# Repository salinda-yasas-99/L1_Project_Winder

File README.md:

# The Winder
Level 01 hardware project_ University of Moratuwa

Here is the system that is able to automate the process of winding transformers. Also, the system is able to measure transformer bobbin parameters and decide on relevant wire gauges according to the transformer input and output.

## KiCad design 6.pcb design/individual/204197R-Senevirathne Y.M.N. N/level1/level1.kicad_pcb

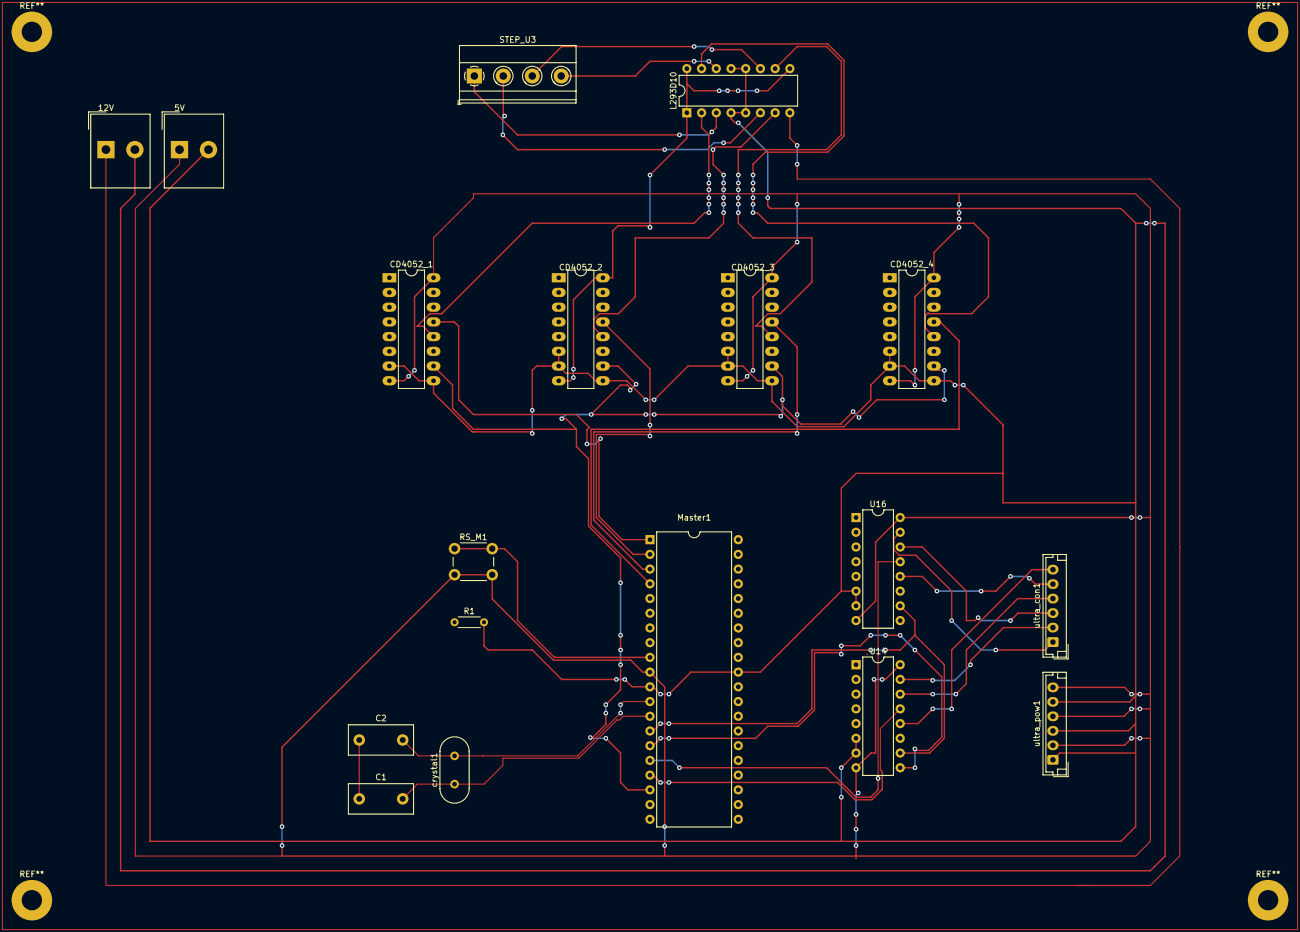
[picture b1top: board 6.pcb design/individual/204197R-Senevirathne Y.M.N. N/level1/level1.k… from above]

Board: 2 copper layers, 18 parts (0 on the bottom side), 30 nets.

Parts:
5V: 5V; Altech_AK300_1x02_P5.00mm_45-Degree
12V: 12V; Altech_AK300_1x02_P5.00mm_45-Degree
C1, C2: 22 uf; C_Disc_D11.0mm_W5.0mm_P7.50mm
CD4052_1, CD4052_2, CD4052_3, CD4052_4: CD4052B; DIP-16_W7.62mm_LongPads
L293D10: L293D; DIP-16_W7.62mm
Master1: ATmega32-16P; DIP-40_W15.24mm
R1: 1k; R_Axial_DIN0204_L3.6mm_D1.6mm_P5.08mm_Horizontal
RS_M1: SW_Push; SW_PUSH_6mm_H7.3mm
STEP_U3: Screw_Terminal_01x04; TerminalBlock_Phoenix_MKDS-1,5-4_1x04_P5.00mm_Horizontal
U14, U16: CD4052B; DIP-16_W7.62mm
crystal1: 16Mhz; Crystal_HC49-4H_Vertical
ultra_con1: Conn_01x06_Female; JST_EH_B6B-EH-A_1x06_P2.50mm_Vertical
ultra_pow1: Conn_01x06_Female; JST_EH_B6B-EH-A_1x06_P2.50mm_Vertical

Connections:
5VCC: 5V.1, CD4052_1.8 (VSS), CD4052_1.16 (VDD), CD4052_2.8 (VSS), CD4052_2.16 (VDD), CD4052_3.8 (VSS), CD4052_3.16 (VDD), CD4052_4.8 (VSS), CD4052_4.16 (VDD), L293D10.1 (EN1,2), L293D10.9 (EN3,4), L293D10.16 (VCC1), Master1.10 (VCC), RS_M1.2, U14.8 (VSS), U14.16 (VDD), U16.8 (VSS), U16.16 (VDD), ultra_pow1.2, ultra_pow1.4, ultra_pow1.6
12VCC: 12V.1, L293D10.8 (VCC2)
GND: 5V.2, 12V.2, CD4052_1.6 (INH), CD4052_1.7 (VEE), CD4052_1.9 (B), CD4052_2.6 (INH), CD4052_2.7 (VEE), CD4052_2.9 (B), CD4052_3.6 (INH), CD4052_3.7 (VEE), CD4052_3.9 (B), CD4052_4.6 (INH), CD4052_4.7 (VEE), CD4052_4.9 (B), L293D10.4 (GND), L293D10.5 (GND), L293D10.12 (GND), L293D10.13 (GND), Master1.11 (GND), Master1.31 (GND), R1.2, U14.6 (INH), U14.7 (VEE), U16.6 (INH), U16.7 (VEE), ultra_pow1.1, ultra_pow1.3, ultra_pow1.5
unnamed: C1.1, C2.1
Reset_M: Master1.9 (~RESET), R1.1, RS_M1.1
STEP2_demux_IN1: CD4052_1.13 (X), Master1.1 (PB0)
STEP2_demux_IN2: CD4052_2.13 (X), Master1.2 (PB1)
STEP2_demux_IN3: CD4052_3.13 (X), Master1.3 (PB2)
STEP2_demux_IN4: CD4052_4.13 (X), Master1.4 (PB3)
Stepper_demux_selector: CD4052_1.10 (A), CD4052_2.10 (A), CD4052_3.10 (A), CD4052_4.10 (A), Master1.18 (PD4)
U1_Echo: U16.12 (X0), ultra_con1.5
U1_Tri: U14.12 (X0), ultra_con1.6
U2_Echo: U16.14 (X1), ultra_con1.3
U2_Tri: U14.14 (X1), ultra_con1.4
U3_Echo: U16.15 (X2), ultra_con1.1
U3_Tri: U14.15 (X2), ultra_con1.2
U3_in_1: CD4052_1.12 (X0), L293D10.2 (1A)
U3_in_2: CD4052_2.12 (X0), L293D10.7 (2A)
U3_in_3: CD4052_3.12 (X0), L293D10.10 (3A)
U3_in_4: CD4052_4.12 (X0), L293D10.15 (4A)
U3_out1: L293D10.3 (1Y), STEP_U3.1
U3_out2: L293D10.6 (2Y), STEP_U3.2
U3_out3: L293D10.11 (3Y), STEP_U3.3
U3_out4: L293D10.14 (4Y), STEP_U3.4
Ultra_demux_input: Master1.17 (PD3), U14.13 (X)
Ultra_mux_input: Master1.16 (PD2), U16.13 (X)
ultra_S1: Master1.14 (PD0), U14.10 (A), U16.10 (A)
ultra_S2: Master1.15 (PD1), U14.9 (B), U16.9 (B)
xtal1_M: C1.2, Master1.13 (XTAL1), crystal1.1
xtal2_M: C2.2, Master1.12 (XTAL2), crystal1.2

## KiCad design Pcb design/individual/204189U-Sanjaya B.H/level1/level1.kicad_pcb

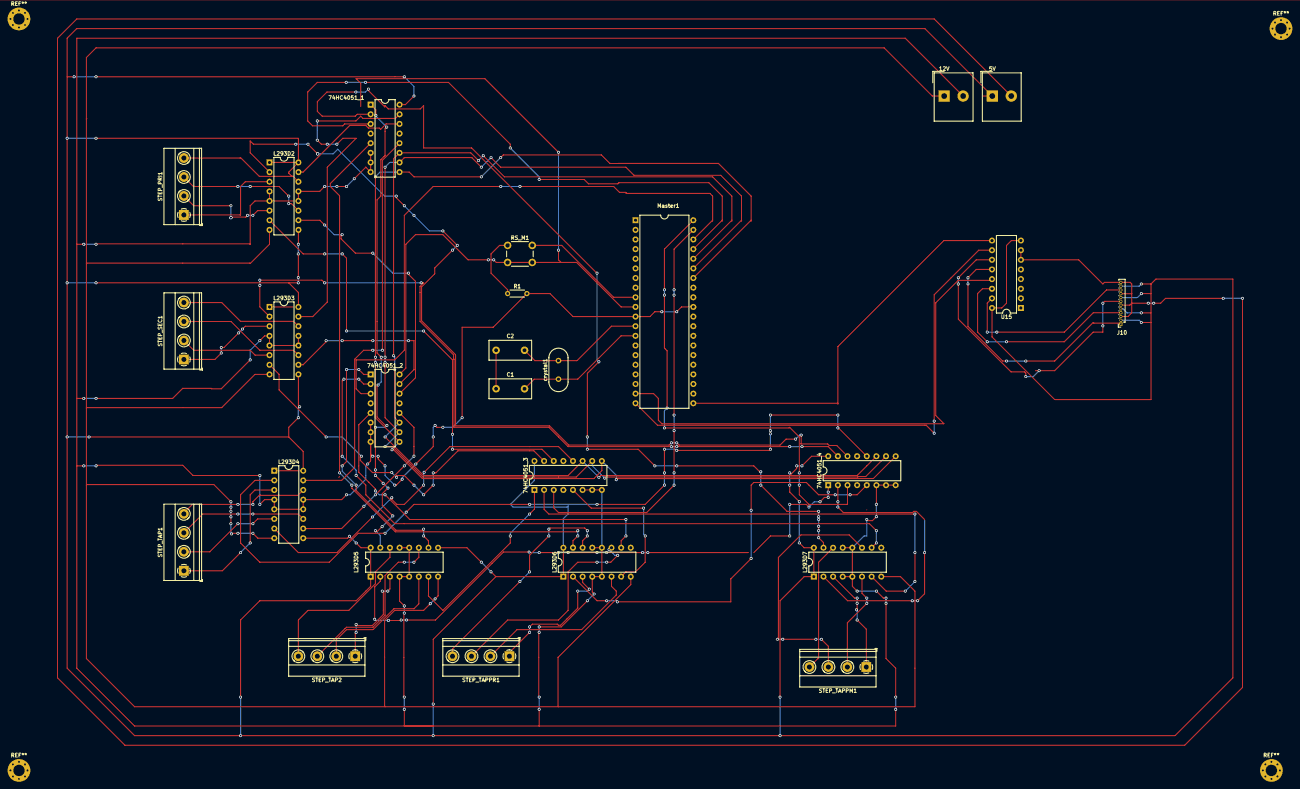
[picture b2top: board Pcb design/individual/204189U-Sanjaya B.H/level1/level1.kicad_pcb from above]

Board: 2 copper layers, 26 parts (0 on the bottom side), 41 nets.

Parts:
5V: 5V; Altech_AK300_1x02_P5.00mm_45-Degree
12V: 12V; Altech_AK300_1x02_P5.00mm_45-Degree
74HC4051_1, 74HC4051_2, 74HC4051_3, 74HC4051_4: 74HCT4051; DIP-16_W7.62mm
C1, C2: 22 uf; C_Disc_D11.0mm_W5.0mm_P7.50mm
J10: Servo; PinSocket_1x12_P1.00mm_Vertical
L293D2, L293D3, L293D4, L293D5, L293D6, L293D7: L293D; DIP-16_W7.62mm
Master1: ATmega32-16P; DIP-40_W15.24mm
R1: 1k; R_Axial_DIN0204_L3.6mm_D1.6mm_P5.08mm_Horizontal
RS_M1: SW_Push; SW_PUSH_6mm_H7.3mm
STEP_PRI1: Screw_Terminal_01x04; TerminalBlock_Phoenix_MKDS-1,5-4_1x04_P5.00mm_Horizontal
STEP_SEC1: Screw_Terminal_01x04; TerminalBlock_Phoenix_MKDS-1,5-4_1x04_P5.00mm_Horizontal
STEP_TAP1, STEP_TAP2: Screw_Terminal_01x04; TerminalBlock_Phoenix_MKDS-1,5-4_1x04_P5.00mm_Horizontal
STEP_TAPPM1: Screw_Terminal_01x04; TerminalBlock_Phoenix_MKDS-1,5-4_1x04_P5.00mm_Horizontal
STEP_TAPPR1: Screw_Terminal_01x04; TerminalBlock_Phoenix_MKDS-1,5-4_1x04_P5.00mm_Horizontal
U15: CD4052B; DIP-16_W7.62mm
crystal1: 16Mhz; Crystal_HC49-4H_Vertical

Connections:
5VCC: 5V.1, 74HC4051_1.16 (VCC), 74HC4051_2.16 (VCC), 74HC4051_3.16 (VCC), 74HC4051_4.16 (VCC), J10.2, J10.5, J10.8, J10.11, L293D2.1 (EN1,2), L293D2.9 (EN3,4), L293D2.16 (VCC1), L293D3.1 (EN1,2), L293D3.9 (EN3,4), L293D3.16 (VCC1), L293D4.1 (EN1,2), L293D4.9 (EN3,4), L293D4.16 (VCC1), L293D5.1 (EN1,2), L293D5.9 (EN3,4), L293D5.16 (VCC1), L293D6.1 (EN1,2), L293D6.9 (EN3,4), L293D6.16 (VCC1), L293D7.1 (EN1,2), L293D7.9 (EN3,4), L293D7.16 (VCC1), Master1.10 (VCC), RS_M1.2, U15.8 (VSS), U15.16 (VDD)
12VCC: 12V.1, L293D2.8 (VCC2), L293D3.8 (VCC2), L293D4.8 (VCC2), L293D5.8 (VCC2), L293D6.8 (VCC2), L293D7.8 (VCC2)
DEMUX_Servo_IN: Master1.19 (PD5), U15.13 (X)
DEMUX_Servo_S1: Master1.20 (PD6), U15.10 (A)
DEMUX_Servo_S2: Master1.21 (PD7), U15.9 (B)
DEMUX_Stepper_S1: 74HC4051_1.11 (S0), 74HC4051_2.11 (S0), 74HC4051_3.11 (S0), 74HC4051_4.11 (S0), Master1.36 (PA4)
DEMUX_Stepper_S2: 74HC4051_1.10 (S1), 74HC4051_2.10 (S1), 74HC4051_3.10 (S1), 74HC4051_4.10 (S1), Master1.35 (PA5)
DEMUX_Stepper_S3: 74HC4051_1.9 (S2), 74HC4051_2.9 (S2), 74HC4051_3.9 (S2), 74HC4051_4.9 (S2), Master1.34 (PA6)
GND: 5V.2, 12V.2, 74HC4051_1.6 (~E), 74HC4051_1.7 (VEE), 74HC4051_1.8 (GND), 74HC4051_2.6 (~E), 74HC4051_2.7 (VEE), 74HC4051_2.8 (GND), 74HC4051_3.6 (~E), 74HC4051_3.7 (VEE), 74HC4051_3.8 (GND), 74HC4051_4.6 (~E), 74HC4051_4.7 (VEE), 74HC4051_4.8 (GND), J10.3, J10.6, J10.9, J10.12, L293D2.4 (GND), L293D2.5 (GND), L293D2.12 (GND), L293D2.13 (GND), L293D3.4 (GND), L293D3.5 (GND), L293D3.12 (GND), L293D3.13 (GND), L293D4.4 (GND), L293D4.5 (GND), L293D4.12 (GND), L293D4.13 (GND), L293D5.4 (GND), L293D5.5 (GND), L293D5.12 (GND), L293D5.13 (GND), L293D6.4 (GND), L293D6.5 (GND), L293D6.12 (GND), L293D6.13 (GND), L293D7.4 (GND), L293D7.5 (GND), L293D7.12 (GND), L293D7.13 (GND), Master1.11 (GND), Master1.31 (GND), R1.2, U15.6 (INH), U15.7 (VEE)
unnamed: C1.1, C2.1
Pri_IN1: 74HC4051_4.14 (A1), L293D2.2 (1A)
Pri_IN2: 74HC4051_3.14 (A1), L293D2.7 (2A)
Pri_IN3: 74HC4051_2.14 (A1), L293D2.10 (3A)
Pri_IN4: 74HC4051_1.14 (A1), L293D2.15 (4A)
Reset_M: Master1.9 (~RESET), R1.1, RS_M1.1
Sec_IN1: 74HC4051_4.15 (A2), L293D3.2 (1A)
Sec_IN2: 74HC4051_3.15 (A2), L293D3.7 (2A)
Sec_IN3: 74HC4051_2.15 (A2), L293D3.10 (3A)
Sec_IN4: 74HC4051_1.15 (A2), L293D3.15 (4A)
Step_IN1: 74HC4051_4.3 (A), Master1.40 (PA0)
Step_IN2: 74HC4051_3.3 (A), Master1.39 (PA1)
Step_IN3: 74HC4051_2.3 (A), Master1.38 (PA2)
Step_IN4: 74HC4051_1.3 (A), Master1.37 (PA3)
TAPM_IN1: 74HC4051_4.2 (A6), L293D7.2 (1A)
TAPM_IN2: 74HC4051_3.2 (A6), L293D7.7 (2A)
TAPM_IN3: 74HC4051_2.2 (A6), L293D7.10 (3A)
TAPM_IN4: 74HC4051_1.2 (A6), L293D7.15 (4A)
TAPR_IN1: 74HC4051_4.5 (A5), L293D6.2 (1A)
TAPR_IN2: 74HC4051_3.5 (A5), L293D6.7 (2A)
TAPR_IN3: 74HC4051_2.5 (A5), L293D6.10 (3A)
TAPR_IN4: 74HC4051_1.5 (A5), L293D6.15 (4A)
Tape1_IN1: 74HC4051_4.12 (A3), L293D4.2 (1A)
Tape1_IN2: 74HC4051_3.12 (A3), L293D4.7 (2A)
Tape1_IN3: 74HC4051_2.12 (A3), L293D4.10 (3A)
Tape1_IN4: 74HC4051_1.12 (A3), L293D4.15 (4A)
Tape2_IN1: 74HC4051_4.1 (A4), L293D5.2 (1A)
Tape2_IN2: 74HC4051_3.1 (A4), L293D5.7 (2A)
Tape2_IN3: 74HC4051_2.1 (A4), L293D5.10 (3A)
Tape2_IN4: 74HC4051_1.1 (A4), L293D5.15 (4A)
xtal1_M: C1.2, Master1.13 (XTAL1), crystal1.1
xtal2_M: C2.2, Master1.12 (XTAL2), crystal1.2

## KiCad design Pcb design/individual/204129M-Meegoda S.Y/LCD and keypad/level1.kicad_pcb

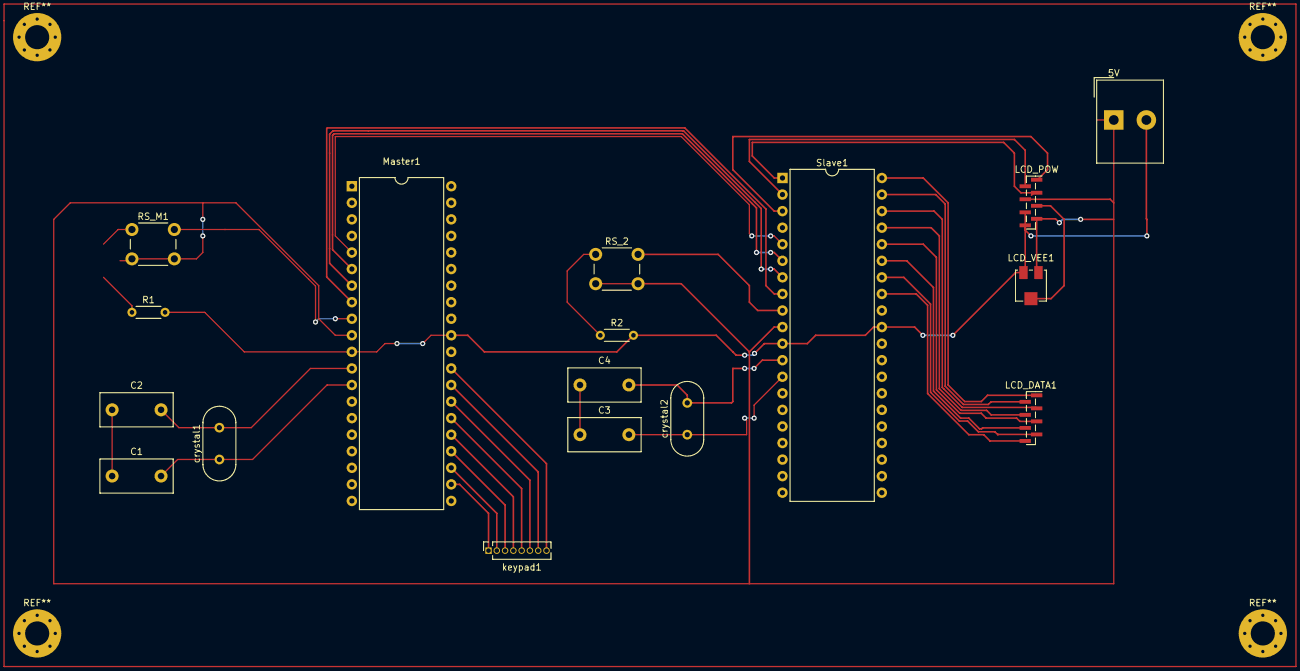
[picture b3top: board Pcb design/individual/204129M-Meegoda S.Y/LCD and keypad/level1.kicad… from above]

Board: 2 copper layers, 17 parts (0 on the bottom side), 34 nets.

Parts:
5V: 5V; Altech_AK300_1x02_P5.00mm_45-Degree
C1, C2, C3, C4: 22 uf; C_Disc_D11.0mm_W5.0mm_P7.50mm
LCD_DATA1: Conn_01x08_Female; PinHeader_1x08_P1.00mm_Vertical_SMD_Pin1Right
LCD_POW: Conn_01x08_Female; PinHeader_1x08_P1.00mm_Vertical_SMD_Pin1Right
LCD_VEE1: R_Potentiometer; Potentiometer_Bourns_3314J_Vertical
Master1: ATmega32-16P; DIP-40_W15.24mm
R1, R2: 1k; R_Axial_DIN0204_L3.6mm_D1.6mm_P5.08mm_Horizontal
RS_2: SW_Push; SW_PUSH_6mm_H7.3mm
RS_M1: SW_Push; SW_PUSH_6mm_H7.3mm
Slave1: ATmega32-16P; DIP-40_W15.24mm
crystal1, crystal2: 16Mhz; Crystal_HC49-4H_Vertical
keypad1: Conn_01x08_Female; PinSocket_1x08_P1.27mm_Vertical

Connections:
5VCC: 5V.1, LCD_POW.4, LCD_POW.7, LCD_VEE1.1, Master1.10 (VCC), RS_2.2, RS_M1.2, Slave1.10 (VCC)
En: LCD_POW.1, Slave1.3 (PB2)
GND: 5V.2, LCD_POW.6, LCD_POW.8, LCD_VEE1.3, Master1.11 (GND), Master1.31 (GND), R1.2, R2.2, Slave1.11 (GND), Slave1.31 (GND)
LCD_D0: LCD_DATA1.1, Slave1.40 (PA0)
LCD_D1: LCD_DATA1.2, Slave1.39 (PA1)
LCD_D2: LCD_DATA1.3, Slave1.38 (PA2)
LCD_D3: LCD_DATA1.4, Slave1.37 (PA3)
LCD_D4: LCD_DATA1.5, Slave1.36 (PA4)
LCD_D5: LCD_DATA1.6, Slave1.35 (PA5)
LCD_D6: LCD_DATA1.7, Slave1.34 (PA6)
LCD_D7: LCD_DATA1.8, Slave1.33 (PA7)
MISO: Master1.7 (PB6), Slave1.7 (PB6)
MOSI: Master1.6 (PB5), Slave1.6 (PB5)
unnamed: C1.1, C2.1
unnamed: C3.1, C4.1
RS: LCD_POW.3, Slave1.1 (PB0)
RW: LCD_POW.2, Slave1.2 (PB1)
Reset_M: Master1.9 (~RESET), R1.1, RS_M1.1
Reset_S: R2.1, RS_2.1, Slave1.9 (~RESET)
SCK: Master1.8 (PB7), Slave1.8 (PB7)
SS: Master1.5 (PB4), Slave1.5 (PB4)
VEE: LCD_POW.5, LCD_VEE1.2
key1: Master1.22 (PC0), keypad1.1
key2: Master1.23 (PC1), keypad1.2
key3: Master1.24 (PC2), keypad1.3
key4: Master1.25 (PC3), keypad1.4
key5: Master1.26 (PC4), keypad1.5
key6: Master1.27 (PC5), keypad1.6
key7: Master1.28 (PC6), keypad1.7
key8: Master1.29 (PC7), keypad1.8
xtal1_M: C1.2, Master1.13 (XTAL1), crystal1.1
xtal1_S: C3.2, Slave1.13 (XTAL1), crystal2.1
xtal2_M: C2.2, Master1.12 (XTAL2), crystal1.2
xtal2_S: C4.2, Slave1.12 (XTAL2), crystal2.2

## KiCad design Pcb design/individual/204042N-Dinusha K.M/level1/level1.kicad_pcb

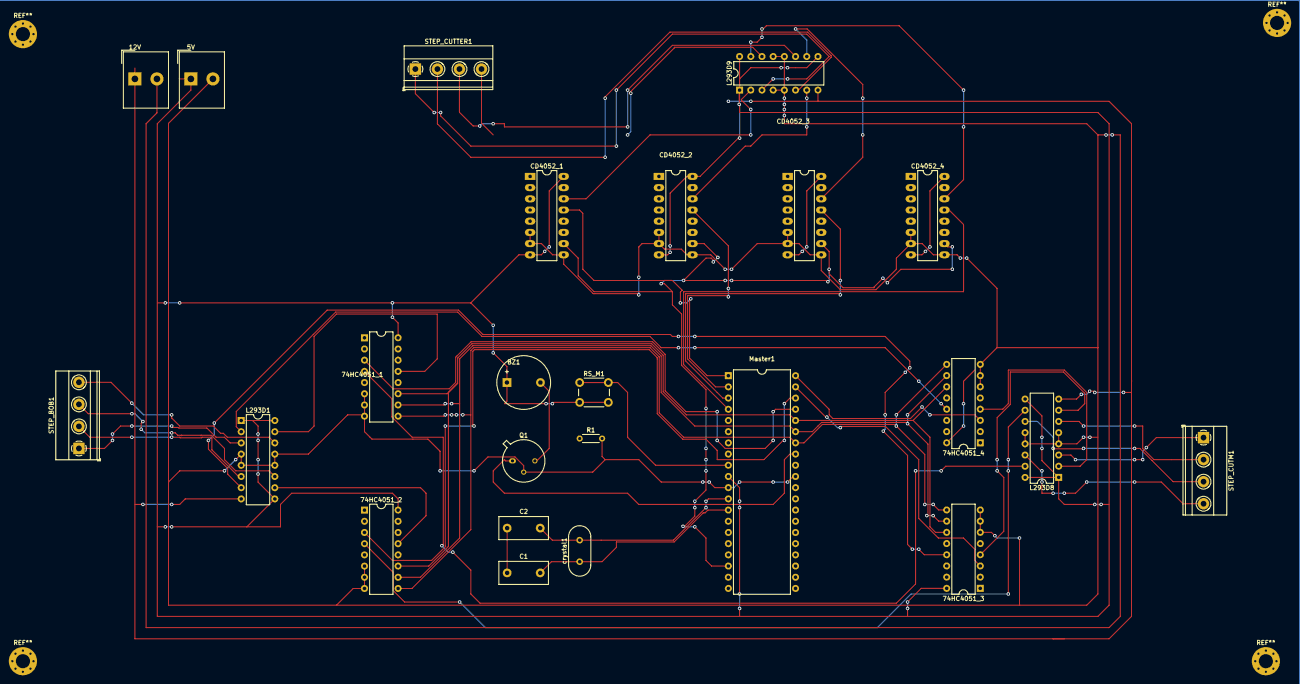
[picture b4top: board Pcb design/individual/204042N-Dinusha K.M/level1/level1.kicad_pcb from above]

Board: 2 copper layers, 24 parts (0 on the bottom side), 45 nets.

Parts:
5V: 5V; Altech_AK300_1x02_P5.00mm_45-Degree
12V: 12V; Altech_AK300_1x02_P5.00mm_45-Degree
74HC4051_1, 74HC4051_2, 74HC4051_3, 74HC4051_4: 74HCT4051; DIP-16_W7.62mm
BZ1: Buzzer; Buzzer_12x9.5RM7.6
C1, C2: 22 uf; C_Disc_D11.0mm_W5.0mm_P7.50mm
CD4052_1, CD4052_2, CD4052_3, CD4052_4: CD4052B; DIP-16_W7.62mm_LongPads
L293D1, L293D8, L293D9: L293D; DIP-16_W7.62mm
Master1: ATmega32-16P; DIP-40_W15.24mm
Q1: 2N3055; TO-39-3_Window
R1: 1k; R_Axial_DIN0204_L3.6mm_D1.6mm_P5.08mm_Horizontal
RS_M1: SW_Push; SW_PUSH_6mm_H7.3mm
STEP_BOB1: Screw_Terminal_01x04; TerminalBlock_Phoenix_MKDS-1,5-4_1x04_P5.00mm_Horizontal
STEP_CUTM1: Screw_Terminal_01x04; TerminalBlock_Phoenix_MKDS-1,5-4_1x04_P5.00mm_Horizontal
STEP_CUTTER1: Screw_Terminal_01x04; TerminalBlock_Phoenix_MKDS-1,5-4_1x04_P5.00mm_Horizontal
crystal1: 16Mhz; Crystal_HC49-4H_Vertical

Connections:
5VCC: 5V.1, 74HC4051_1.16 (VCC), 74HC4051_2.16 (VCC), 74HC4051_3.16 (VCC), 74HC4051_4.16 (VCC), BZ1.1 (-), CD4052_1.8 (VSS), CD4052_1.16 (VDD), CD4052_2.8 (VSS), CD4052_2.16 (VDD), CD4052_3.8 (VSS), CD4052_3.16 (VDD), CD4052_4.8 (VSS), CD4052_4.16 (VDD), L293D1.1 (EN1,2), L293D1.9 (EN3,4), L293D1.16 (VCC1), L293D8.1 (EN1,2), L293D8.9 (EN3,4), L293D8.16 (VCC1), L293D9.1 (EN1,2), L293D9.9 (EN3,4), L293D9.16 (VCC1), Master1.10 (VCC), RS_M1.2
12VCC: 12V.1, L293D1.8 (VCC2), L293D8.8 (VCC2), L293D9.8 (VCC2)
BUZ: Master1.33 (PA7), Q1.1 (B)
Bobbin_IN1: 74HC4051_4.13 (A0), L293D1.2 (1A)
Bobbin_IN2: 74HC4051_3.13 (A0), L293D1.7 (2A)
Bobbin_IN3: 74HC4051_2.13 (A0), L293D1.10 (3A)
Bobbin_IN4: 74HC4051_1.13 (A0), L293D1.15 (4A)
Bobbin_OUT1: L293D1.3 (1Y), STEP_BOB1.1
Bobbin_OUT2: L293D1.6 (2Y), STEP_BOB1.2
Bobbin_OUT3: L293D1.11 (3Y), STEP_BOB1.3
Bobbin_OUT4: L293D1.14 (4Y), STEP_BOB1.4
DEMUX_Stepper_S1: 74HC4051_1.11 (S0), 74HC4051_2.11 (S0), 74HC4051_3.11 (S0), 74HC4051_4.11 (S0), Master1.36 (PA4)
DEMUX_Stepper_S2: 74HC4051_1.10 (S1), 74HC4051_2.10 (S1), 74HC4051_3.10 (S1), 74HC4051_4.10 (S1), Master1.35 (PA5)
DEMUX_Stepper_S3: 74HC4051_1.9 (S2), 74HC4051_2.9 (S2), 74HC4051_3.9 (S2), 74HC4051_4.9 (S2), Master1.34 (PA6)
GND: 5V.2, 12V.2, 74HC4051_1.6 (~E), 74HC4051_1.7 (VEE), 74HC4051_1.8 (GND), 74HC4051_2.6 (~E), 74HC4051_2.7 (VEE), 74HC4051_2.8 (GND), 74HC4051_3.6 (~E), 74HC4051_3.7 (VEE), 74HC4051_3.8 (GND), 74HC4051_4.6 (~E), 74HC4051_4.7 (VEE), 74HC4051_4.8 (GND), CD4052_1.6 (INH), CD4052_1.7 (VEE), CD4052_1.9 (B), CD4052_2.6 (INH), CD4052_2.7 (VEE), CD4052_2.9 (B), CD4052_3.6 (INH), CD4052_3.7 (VEE), CD4052_3.9 (B), CD4052_4.6 (INH), CD4052_4.7 (VEE), CD4052_4.9 (B), L293D1.4 (GND), L293D1.5 (GND), L293D1.12 (GND), L293D1.13 (GND), L293D8.4 (GND), L293D8.5 (GND), L293D8.12 (GND), L293D8.13 (GND), L293D9.4 (GND), L293D9.5 (GND), L293D9.12 (GND), L293D9.13 (GND), Master1.11 (GND), Master1.31 (GND), Q1.2 (E), R1.2
unnamed: BZ1.2 (+), Q1.3 (C)
unnamed: C1.1, C2.1
Reset_M: Master1.9 (~RESET), R1.1, RS_M1.1
STEP2_demux_IN1: CD4052_1.13 (X), Master1.1 (PB0)
STEP2_demux_IN2: CD4052_2.13 (X), Master1.2 (PB1)
STEP2_demux_IN3: CD4052_3.13 (X), Master1.3 (PB2)
STEP2_demux_IN4: CD4052_4.13 (X), Master1.4 (PB3)
Step_IN1: 74HC4051_4.3 (A), Master1.40 (PA0)
Step_IN2: 74HC4051_3.3 (A), Master1.39 (PA1)
Step_IN3: 74HC4051_2.3 (A), Master1.38 (PA2)
Step_IN4: 74HC4051_1.3 (A), Master1.37 (PA3)
Stepper_demux_selector: CD4052_1.10 (A), CD4052_2.10 (A), CD4052_3.10 (A), CD4052_4.10 (A), Master1.18 (PD4)
cutROT_in_1: CD4052_1.14 (X1), L293D9.2 (1A)
cutROT_in_2: CD4052_2.14 (X1), L293D9.7 (2A)
cutROT_in_3: CD4052_3.14 (X1), L293D9.10 (3A)
cutROT_in_4: CD4052_4.14 (X1), L293D9.15 (4A)
cutROT_out1: L293D9.3 (1Y), STEP_CUTTER1.1
cutROT_out2: L293D9.6 (2Y), STEP_CUTTER1.2
cutROT_out3: L293D9.11 (3Y), STEP_CUTTER1.3
cutROT_out4: L293D9.14 (4Y), STEP_CUTTER1.4
cut_IN1: 74HC4051_4.4 (A7), L293D8.2 (1A)
cut_IN2: 74HC4051_3.4 (A7), L293D8.7 (2A)
cut_IN3: 74HC4051_2.4 (A7), L293D8.10 (3A)
cut_IN4: 74HC4051_1.4 (A7), L293D8.15 (4A)
cut_out1: L293D8.3 (1Y), STEP_CUTM1.1
cut_out2: L293D8.6 (2Y), STEP_CUTM1.2
cut_out3: L293D8.11 (3Y), STEP_CUTM1.3
cut_out4: L293D8.14 (4Y), STEP_CUTM1.4
xtal1_M: C1.2, Master1.13 (XTAL1), crystal1.1
xtal2_M: C2.2, Master1.12 (XTAL2), crystal1.2

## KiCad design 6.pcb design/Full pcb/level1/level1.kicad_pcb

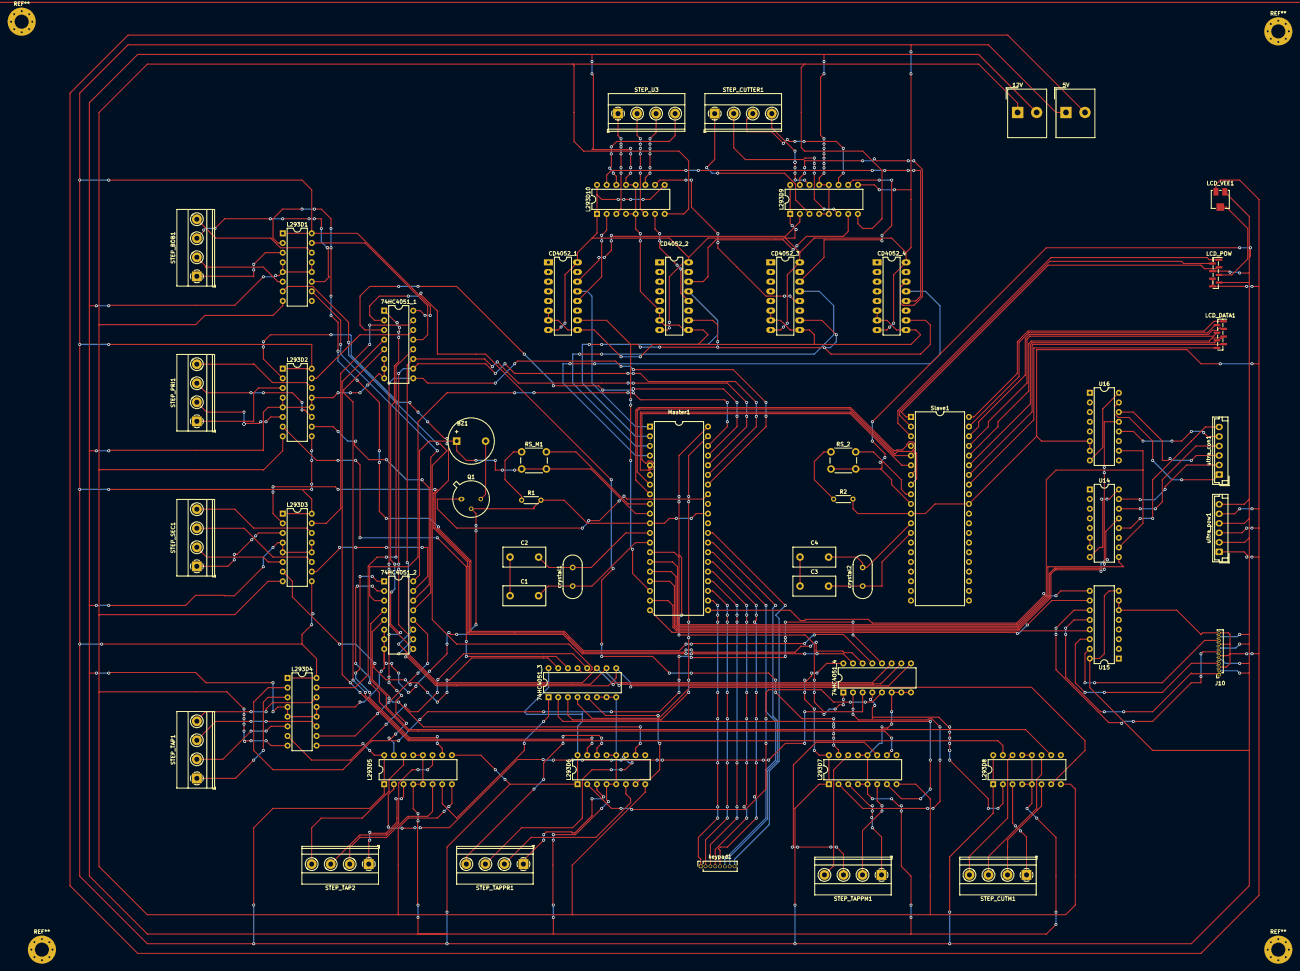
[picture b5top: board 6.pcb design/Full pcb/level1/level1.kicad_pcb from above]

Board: 2 copper layers, 54 parts (0 on the bottom side), 146 nets.

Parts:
5V: 5V; Altech_AK300_1x02_P5.00mm_45-Degree
12V: 12V; Altech_AK300_1x02_P5.00mm_45-Degree
74HC4051_1, 74HC4051_2, 74HC4051_3, 74HC4051_4: 74HCT4051; DIP-16_W7.62mm
BZ1: Buzzer; Buzzer_12x9.5RM7.6
C1, C2, C3, C4: 22 uf; C_Disc_D11.0mm_W5.0mm_P7.50mm
CD4052_1, CD4052_2, CD4052_3, CD4052_4: CD4052B; DIP-16_W7.62mm_LongPads
J10: Servo; PinSocket_1x12_P1.00mm_Vertical
L293D1, L293D2, L293D3, L293D4, L293D5, L293D6, L293D7, L293D8, L293D9, L293D10: L293D; DIP-16_W7.62mm
LCD_DATA1: Conn_01x08_Female; PinHeader_1x08_P1.00mm_Vertical_SMD_Pin1Right
LCD_POW: Conn_01x08_Female; PinHeader_1x08_P1.00mm_Vertical_SMD_Pin1Right
LCD_VEE1: R_Potentiometer; Potentiometer_Bourns_3314J_Vertical
Master1: ATmega32-16P; DIP-40_W15.24mm
Q1: 2N3055; TO-39-3_Window
R1, R2: 1k; R_Axial_DIN0204_L3.6mm_D1.6mm_P5.08mm_Horizontal
RS_2: SW_Push; SW_PUSH_6mm_H7.3mm
RS_M1: SW_Push; SW_PUSH_6mm_H7.3mm
STEP_BOB1: Screw_Terminal_01x04; TerminalBlock_Phoenix_MKDS-1,5-4_1x04_P5.00mm_Horizontal
STEP_CUTM1: Screw_Terminal_01x04; TerminalBlock_Phoenix_MKDS-1,5-4_1x04_P5.00mm_Horizontal
STEP_CUTTER1: Screw_Terminal_01x04; TerminalBlock_Phoenix_MKDS-1,5-4_1x04_P5.00mm_Horizontal
STEP_PRI1: Screw_Terminal_01x04; TerminalBlock_Phoenix_MKDS-1,5-4_1x04_P5.00mm_Horizontal
STEP_SEC1: Screw_Terminal_01x04; TerminalBlock_Phoenix_MKDS-1,5-4_1x04_P5.00mm_Horizontal
STEP_TAP1, STEP_TAP2: Screw_Terminal_01x04; TerminalBlock_Phoenix_MKDS-1,5-4_1x04_P5.00mm_Horizontal
STEP_TAPPM1: Screw_Terminal_01x04; TerminalBlock_Phoenix_MKDS-1,5-4_1x04_P5.00mm_Horizontal
STEP_TAPPR1: Screw_Terminal_01x04; TerminalBlock_Phoenix_MKDS-1,5-4_1x04_P5.00mm_Horizontal
STEP_U3: Screw_Terminal_01x04; TerminalBlock_Phoenix_MKDS-1,5-4_1x04_P5.00mm_Horizontal
Slave1: ATmega32-16P; DIP-40_W15.24mm
U14, U15, U16: CD4052B; DIP-16_W7.62mm
crystal1, crystal2: 16Mhz; Crystal_HC49-4H_Vertical
keypad1: Conn_01x08_Female; PinSocket_1x08_P1.27mm_Vertical
ultra_con1: Conn_01x06_Female; JST_EH_B6B-EH-A_1x06_P2.50mm_Vertical
ultra_pow1: Conn_01x06_Female; JST_EH_B6B-EH-A_1x06_P2.50mm_Vertical

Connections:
5VCC: 5V.1, 74HC4051_1.16 (VCC), 74HC4051_2.16 (VCC), 74HC4051_3.16 (VCC), 74HC4051_4.16 (VCC), BZ1.1 (-), CD4052_1.8 (VSS), CD4052_1.16 (VDD), CD4052_2.8 (VSS), CD4052_2.16 (VDD), CD4052_3.8 (VSS), CD4052_3.16 (VDD), CD4052_4.8 (VSS), CD4052_4.16 (VDD), J10.2, J10.5, J10.8, J10.11, L293D1.1 (EN1,2), L293D1.9 (EN3,4), L293D1.16 (VCC1), L293D2.1 (EN1,2), L293D2.9 (EN3,4), L293D2.16 (VCC1), L293D3.1 (EN1,2), L293D3.9 (EN3,4), L293D3.16 (VCC1), L293D4.1 (EN1,2), L293D4.9 (EN3,4), L293D4.16 (VCC1), L293D5.1 (EN1,2), L293D5.9 (EN3,4), L293D5.16 (VCC1), L293D6.1 (EN1,2), L293D6.9 (EN3,4), L293D6.16 (VCC1), L293D7.1 (EN1,2), L293D7.9 (EN3,4), L293D7.16 (VCC1), L293D8.1 (EN1,2), L293D8.9 (EN3,4), L293D8.16 (VCC1), L293D9.1 (EN1,2), L293D9.9 (EN3,4), L293D9.16 (VCC1), L293D10.1 (EN1,2), L293D10.9 (EN3,4), L293D10.16 (VCC1), LCD_POW.4, LCD_POW.7, LCD_VEE1.1, Master1.10 (VCC), RS_2.2, RS_M1.2, Slave1.10 (VCC), U14.8 (VSS), U14.16 (VDD), U15.8 (VSS), U15.16 (VDD), U16.8 (VSS), U16.16 (VDD), ultra_pow1.2, ultra_pow1.4, ultra_pow1.6
12VCC: 12V.1, L293D1.8 (VCC2), L293D2.8 (VCC2), L293D3.8 (VCC2), L293D4.8 (VCC2), L293D5.8 (VCC2), L293D6.8 (VCC2), L293D7.8 (VCC2), L293D8.8 (VCC2), L293D9.8 (VCC2), L293D10.8 (VCC2)
BUZ: Master1.33 (PA7), Q1.1 (B)
Bobbin_IN1: 74HC4051_4.13 (A0), L293D1.2 (1A)
Bobbin_IN2: 74HC4051_3.13 (A0), L293D1.7 (2A)
Bobbin_IN3: 74HC4051_2.13 (A0), L293D1.10 (3A)
Bobbin_IN4: 74HC4051_1.13 (A0), L293D1.15 (4A)
Bobbin_OUT1: L293D1.3 (1Y), STEP_BOB1.1
Bobbin_OUT2: L293D1.6 (2Y), STEP_BOB1.2
Bobbin_OUT3: L293D1.11 (3Y), STEP_BOB1.3
Bobbin_OUT4: L293D1.14 (4Y), STEP_BOB1.4
DEMUX_Servo_IN: Master1.19 (PD5), U15.13 (X)
DEMUX_Servo_S1: Master1.20 (PD6), U15.10 (A)
DEMUX_Servo_S2: Master1.21 (PD7), U15.9 (B)
DEMUX_Stepper_S1: 74HC4051_1.11 (S0), 74HC4051_2.11 (S0), 74HC4051_3.11 (S0), 74HC4051_4.11 (S0), Master1.36 (PA4)
DEMUX_Stepper_S2: 74HC4051_1.10 (S1), 74HC4051_2.10 (S1), 74HC4051_3.10 (S1), 74HC4051_4.10 (S1), Master1.35 (PA5)
DEMUX_Stepper_S3: 74HC4051_1.9 (S2), 74HC4051_2.9 (S2), 74HC4051_3.9 (S2), 74HC4051_4.9 (S2), Master1.34 (PA6)
En: LCD_POW.1, Slave1.3 (PB2)
GND: 5V.2, 12V.2, 74HC4051_1.6 (~E), 74HC4051_1.7 (VEE), 74HC4051_1.8 (GND), 74HC4051_2.6 (~E), 74HC4051_2.7 (VEE), 74HC4051_2.8 (GND), 74HC4051_3.6 (~E), 74HC4051_3.7 (VEE), 74HC4051_3.8 (GND), 74HC4051_4.6 (~E), 74HC4051_4.7 (VEE), 74HC4051_4.8 (GND), CD4052_1.6 (INH), CD4052_1.7 (VEE), CD4052_1.9 (B), CD4052_2.6 (INH), CD4052_2.7 (VEE), CD4052_2.9 (B), CD4052_3.6 (INH), CD4052_3.7 (VEE), CD4052_3.9 (B), CD4052_4.6 (INH), CD4052_4.7 (VEE), CD4052_4.9 (B), J10.3, J10.6, J10.9, J10.12, L293D1.4 (GND), L293D1.5 (GND), L293D1.12 (GND), L293D1.13 (GND), L293D2.4 (GND), L293D2.5 (GND), L293D2.12 (GND), L293D2.13 (GND), L293D3.4 (GND), L293D3.5 (GND), L293D3.12 (GND), L293D3.13 (GND), L293D4.4 (GND), L293D4.5 (GND), L293D4.12 (GND), L293D4.13 (GND), L293D5.4 (GND), L293D5.5 (GND), L293D5.12 (GND), L293D5.13 (GND), L293D6.4 (GND), L293D6.5 (GND), L293D6.12 (GND), L293D6.13 (GND), L293D7.4 (GND), L293D7.5 (GND), L293D7.12 (GND), L293D7.13 (GND), L293D8.4 (GND), L293D8.5 (GND), L293D8.12 (GND), L293D8.13 (GND), L293D9.4 (GND), L293D9.5 (GND), L293D9.12 (GND), L293D9.13 (GND), L293D10.4 (GND), L293D10.5 (GND), L293D10.12 (GND), L293D10.13 (GND), LCD_POW.6, LCD_POW.8, LCD_VEE1.3, Master1.11 (GND), Master1.31 (GND), Q1.2 (E), R1.2, R2.2, Slave1.11 (GND), Slave1.31 (GND), U14.6 (INH), U14.7 (VEE), U15.6 (INH), U15.7 (VEE), U16.6 (INH), U16.7 (VEE), ultra_pow1.1, ultra_pow1.3, ultra_pow1.5
LCD_D0: LCD_DATA1.1, Slave1.40 (PA0)
LCD_D1: LCD_DATA1.2, Slave1.39 (PA1)
LCD_D2: LCD_DATA1.3, Slave1.38 (PA2)
LCD_D3: LCD_DATA1.4, Slave1.37 (PA3)
LCD_D4: LCD_DATA1.5, Slave1.36 (PA4)
LCD_D5: LCD_DATA1.6, Slave1.35 (PA5)
LCD_D6: LCD_DATA1.7, Slave1.34 (PA6)
LCD_D7: LCD_DATA1.8, Slave1.33 (PA7)
MISO: Master1.7 (PB6), Slave1.7 (PB6)
MOSI: Master1.6 (PB5), Slave1.6 (PB5)
unnamed: BZ1.2 (+), Q1.3 (C)
unnamed: C1.1, C2.1
unnamed: C3.1, C4.1
Pri_IN1: 74HC4051_4.14 (A1), L293D2.2 (1A)
Pri_IN2: 74HC4051_3.14 (A1), L293D2.7 (2A)
Pri_IN3: 74HC4051_2.14 (A1), L293D2.10 (3A)
Pri_IN4: 74HC4051_1.14 (A1), L293D2.15 (4A)
Pri_out1: L293D2.3 (1Y), STEP_PRI1.1
Pri_out2: L293D2.6 (2Y), STEP_PRI1.2
Pri_out3: L293D2.11 (3Y), STEP_PRI1.3
Pri_out4: L293D2.14 (4Y), STEP_PRI1.4
RS: LCD_POW.3, Slave1.1 (PB0)
RW: LCD_POW.2, Slave1.2 (PB1)
Reset_M: Master1.9 (~RESET), R1.1, RS_M1.1
Reset_S: R2.1, RS_2.1, Slave1.9 (~RESET)
SCK: Master1.8 (PB7), Slave1.8 (PB7)
SS: Master1.5 (PB4), Slave1.5 (PB4)
STEP2_demux_IN1: CD4052_1.13 (X), Master1.1 (PB0)
STEP2_demux_IN2: CD4052_2.13 (X), Master1.2 (PB1)
STEP2_demux_IN3: CD4052_3.13 (X), Master1.3 (PB2)
STEP2_demux_IN4: CD4052_4.13 (X), Master1.4 (PB3)
Sec_IN1: 74HC4051_4.15 (A2), L293D3.2 (1A)
Sec_IN2: 74HC4051_3.15 (A2), L293D3.7 (2A)
Sec_IN3: 74HC4051_2.15 (A2), L293D3.10 (3A)
Sec_IN4: 74HC4051_1.15 (A2), L293D3.15 (4A)
Sec_out1: L293D3.3 (1Y), STEP_SEC1.1
Sec_out2: L293D3.6 (2Y), STEP_SEC1.2
Sec_out3: L293D3.11 (3Y), STEP_SEC1.3
Sec_out4: L293D3.14 (4Y), STEP_SEC1.4
Servo_Parm: J10.1, U15.12 (X0)
Servo_Sarm: J10.4, U15.14 (X1)
Servo_tape1: J10.10, U15.15 (X2)
Servo_tape2: J10.7, U15.11 (X3)
Step_IN1: 74HC4051_4.3 (A), Master1.40 (PA0)
Step_IN2: 74HC4051_3.3 (A), Master1.39 (PA1)
Step_IN3: 74HC4051_2.3 (A), Master1.38 (PA2)
Step_IN4: 74HC4051_1.3 (A), Master1.37 (PA3)
Stepper_demux_selector: CD4052_1.10 (A), CD4052_2.10 (A), CD4052_3.10 (A), CD4052_4.10 (A), Master1.18 (PD4)
TAPM_IN1: 74HC4051_4.2 (A6), L293D7.2 (1A)
TAPM_IN2: 74HC4051_3.2 (A6), L293D7.7 (2A)
TAPM_IN3: 74HC4051_2.2 (A6), L293D7.10 (3A)
TAPM_IN4: 74HC4051_1.2 (A6), L293D7.15 (4A)
TAPM_out1: L293D7.3 (1Y), STEP_TAPPM1.1
TAPM_out2: L293D7.6 (2Y), STEP_TAPPM1.2
TAPM_out3: L293D7.11 (3Y), STEP_TAPPM1.3
TAPM_out4: L293D7.14 (4Y), STEP_TAPPM1.4
TAPR_IN1: 74HC4051_4.5 (A5), L293D6.2 (1A)
TAPR_IN2: 74HC4051_3.5 (A5), L293D6.7 (2A)
TAPR_IN3: 74HC4051_2.5 (A5), L293D6.10 (3A)
TAPR_IN4: 74HC4051_1.5 (A5), L293D6.15 (4A)
TAPR_out1: L293D6.3 (1Y), STEP_TAPPR1.1
TAPR_out2: L293D6.6 (2Y), STEP_TAPPR1.2
TAPR_out3: L293D6.11 (3Y), STEP_TAPPR1.3
TAPR_out4: L293D6.14 (4Y), STEP_TAPPR1.4
Tape1_IN1: 74HC4051_4.12 (A3), L293D4.2 (1A)
Tape1_IN2: 74HC4051_3.12 (A3), L293D4.7 (2A)
Tape1_IN3: 74HC4051_2.12 (A3), L293D4.10 (3A)
Tape1_IN4: 74HC4051_1.12 (A3), L293D4.15 (4A)
Tape1_out1: L293D4.3 (1Y), STEP_TAP1.1
Tape1_out2: L293D4.6 (2Y), STEP_TAP1.2
Tape1_out3: L293D4.11 (3Y), STEP_TAP1.3
Tape1_out4: L293D4.14 (4Y), STEP_TAP1.4
Tape2_IN1: 74HC4051_4.1 (A4), L293D5.2 (1A)
Tape2_IN2: 74HC4051_3.1 (A4), L293D5.7 (2A)
Tape2_IN3: 74HC4051_2.1 (A4), L293D5.10 (3A)
Tape2_IN4: 74HC4051_1.1 (A4), L293D5.15 (4A)
Tape2_out1: L293D5.3 (1Y), STEP_TAP2.1
Tape2_out2: L293D5.6 (2Y), STEP_TAP2.2
Tape2_out3: L293D5.11 (3Y), STEP_TAP2.3
Tape2_out4: L293D5.14 (4Y), STEP_TAP2.4
U1_Echo: U16.12 (X0), ultra_con1.5
U1_Tri: U14.12 (X0), ultra_con1.6
U2_Echo: U16.14 (X1), ultra_con1.3
U2_Tri: U14.14 (X1), ultra_con1.4
U3_Echo: U16.15 (X2), ultra_con1.1
U3_Tri: U14.15 (X2), ultra_con1.2
U3_in_1: CD4052_1.12 (X0), L293D10.2 (1A)
U3_in_2: CD4052_2.12 (X0), L293D10.7 (2A)
U3_in_3: CD4052_3.12 (X0), L293D10.10 (3A)
U3_in_4: CD4052_4.12 (X0), L293D10.15 (4A)
U3_out1: L293D10.3 (1Y), STEP_U3.1
U3_out2: L293D10.6 (2Y), STEP_U3.2
U3_out3: L293D10.11 (3Y), STEP_U3.3
U3_out4: L293D10.14 (4Y), STEP_U3.4
Ultra_demux_input: Master1.17 (PD3), U14.13 (X)
Ultra_mux_input: Master1.16 (PD2), U16.13 (X)
VEE: LCD_POW.5, LCD_VEE1.2
cutROT_in_1: CD4052_1.14 (X1), L293D9.2 (1A)
cutROT_in_2: CD4052_2.14 (X1), L293D9.7 (2A)
cutROT_in_3: CD4052_3.14 (X1), L293D9.10 (3A)
cutROT_in_4: CD4052_4.14 (X1), L293D9.15 (4A)
cutROT_out1: L293D9.3 (1Y), STEP_CUTTER1.1
cutROT_out2: L293D9.6 (2Y), STEP_CUTTER1.2
cutROT_out3: L293D9.11 (3Y), STEP_CUTTER1.3
cutROT_out4: L293D9.14 (4Y), STEP_CUTTER1.4
cut_IN1: 74HC4051_4.4 (A7), L293D8.2 (1A)
cut_IN2: 74HC4051_3.4 (A7), L293D8.7 (2A)
cut_IN3: 74HC4051_2.4 (A7), L293D8.10 (3A)
cut_IN4: 74HC4051_1.4 (A7), L293D8.15 (4A)
cut_out1: L293D8.3 (1Y), STEP_CUTM1.1
cut_out2: L293D8.6 (2Y), STEP_CUTM1.2
cut_out3: L293D8.11 (3Y), STEP_CUTM1.3
cut_out4: L293D8.14 (4Y), STEP_CUTM1.4
key1: Master1.22 (PC0), keypad1.1
key2: Master1.23 (PC1), keypad1.2
key3: Master1.24 (PC2), keypad1.3
key4: Master1.25 (PC3), keypad1.4
key5: Master1.26 (PC4), keypad1.5
key6: Master1.27 (PC5), keypad1.6
key7: Master1.28 (PC6), keypad1.7
key8: Master1.29 (PC7), keypad1.8
ultra_S1: Master1.14 (PD0), U14.10 (A), U16.10 (A)
ultra_S2: Master1.15 (PD1), U14.9 (B), U16.9 (B)
xtal1_M: C1.2, Master1.13 (XTAL1), crystal1.1
xtal1_S: C3.2, Slave1.13 (XTAL1), crystal2.1
xtal2_M: C2.2, Master1.12 (XTAL2), crystal1.2
xtal2_S: C4.2, Slave1.12 (XTAL2), crystal2.2

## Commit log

2023-06-11 Delete unnecessary files
    Delete unnecessary files
2023-06-11 Adding changes
    Adding changes
2023-06-11 Create README.md
    Add description
